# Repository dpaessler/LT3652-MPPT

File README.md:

# LT3652-MPPT
LT3652 based MPPT solar charger for a single LiFePo4 cell 

The LT3652 is a 2A multi chemistry MPPT charger controller from Linear Technology.
You can charge other cells by simply changing the values for R1 - R4 (R1 and R2 actually are _one_ resistor with 223k for LiFePo4) according to the datasheet.
Set the trim potentiometer to 2.8V on pin VIN_REG at full sun on the solar panel.

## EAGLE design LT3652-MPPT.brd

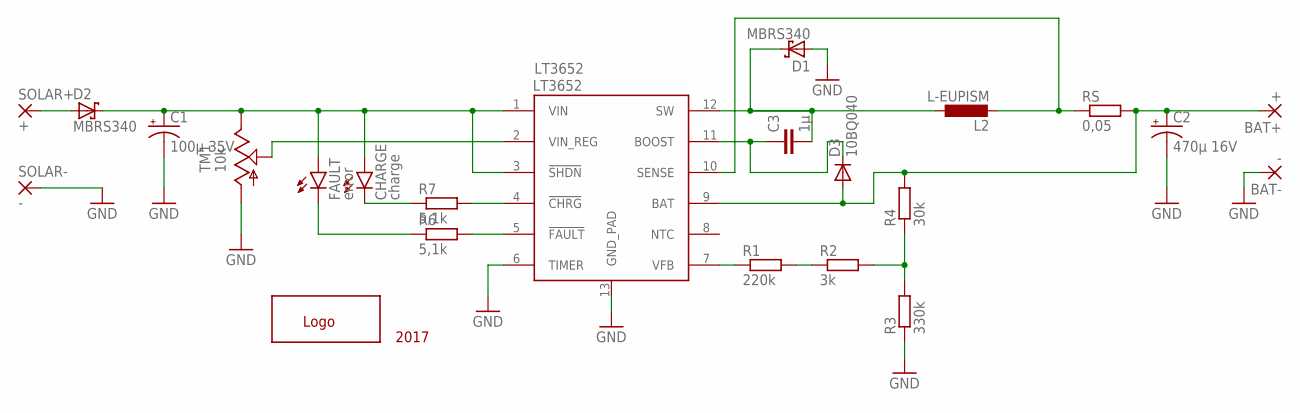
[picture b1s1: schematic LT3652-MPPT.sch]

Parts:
BAT+: +; 3,81/1,4
BAT-: -; 3,81/1,4
C1: 100µ 35V; PANASONIC_C
C2: 470µ 16V; PANASONIC_C
C3: 1µ; C0805
CHARGE: charge; LED-1206
D1, D2: MBRS340; SMC
D3: 10BQ040; SMA-DIODE
FAULT: error; LED-1206
L2: L-EUPISM; PISM
LT3652: LT3652; MSOP-12_GND
R1: 220k; R0805
R2: 3k; R0805
R3: 330k; R0805
R4: 30k; R0805
R6, R7: 5,1k; R0805
RS: 0,05; R1206
SOLAR+: +; 3,81/1,4
SOLAR-: -; 3,81/1,4
TM1: 10k; 5MMP
U$1: 2017; LOGO

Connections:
223K: R1.2, R2.1
BAT: BAT+.1, C2.+, D3.A, LT3652.9 (BAT), R4.2, RS.2
BOOST: C3.1, D3.C, LT3652.11 (BOOST)
CHRG: LT3652.4 (!CHRG), R7.2
DIV: R2.2, R3.2, R4.1
FAULT: LT3652.5 (!FAULT), R6.2
GND: BAT-.1, C1.-, C2.-, D1.A, LT3652.6 (TIMER), LT3652.13 (GND_PAD), R3.1, SOLAR-.1, TM1.A
LEDBLUE: CHARGE.C, R7.1
LEDRED: FAULT.C, R6.1
unnamed: D2.A, SOLAR+.1
SENSE: L2.2, LT3652.10 (SENSE), RS.1
SW: C3.2, D1.C, L2.1, LT3652.12 (SW)
VFB: LT3652.7 (VFB), R1.1
VIN: C1.+, CHARGE.A, D2.C, FAULT.A, LT3652.1 (VIN), LT3652.3 (!SHDN), TM1.E
VREG: LT3652.2 (VIN_REG), TM1.S

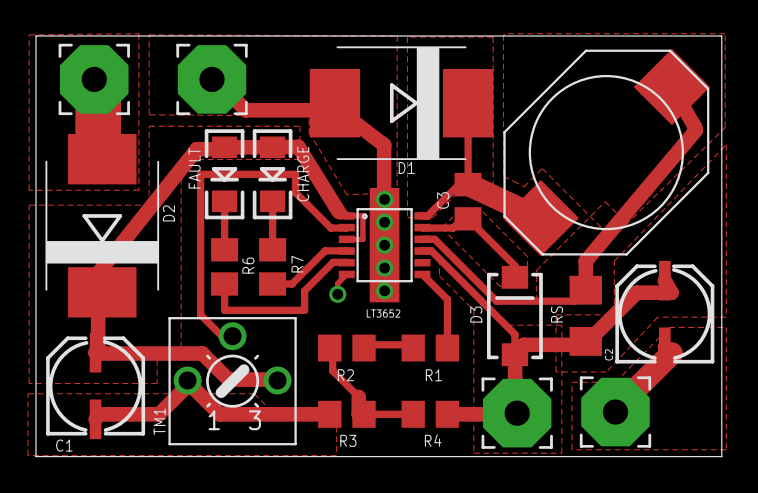
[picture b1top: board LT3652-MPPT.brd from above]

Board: 2 copper layers, 38.1 x 23.4 mm, 23 parts (1 on the bottom side), 15 nets.

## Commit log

2017-09-15 added board and schematic

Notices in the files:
parts and their libraries:
SparkFun: Licensing: CC v3.0 Share-Alike You are welcome to use this library for commercial purposes.
SparkFun-IC-Power: Licensing: Creative Commons ShareAlike 4.0 International - https://creativecommons.org/licenses/by-sa/4.0
